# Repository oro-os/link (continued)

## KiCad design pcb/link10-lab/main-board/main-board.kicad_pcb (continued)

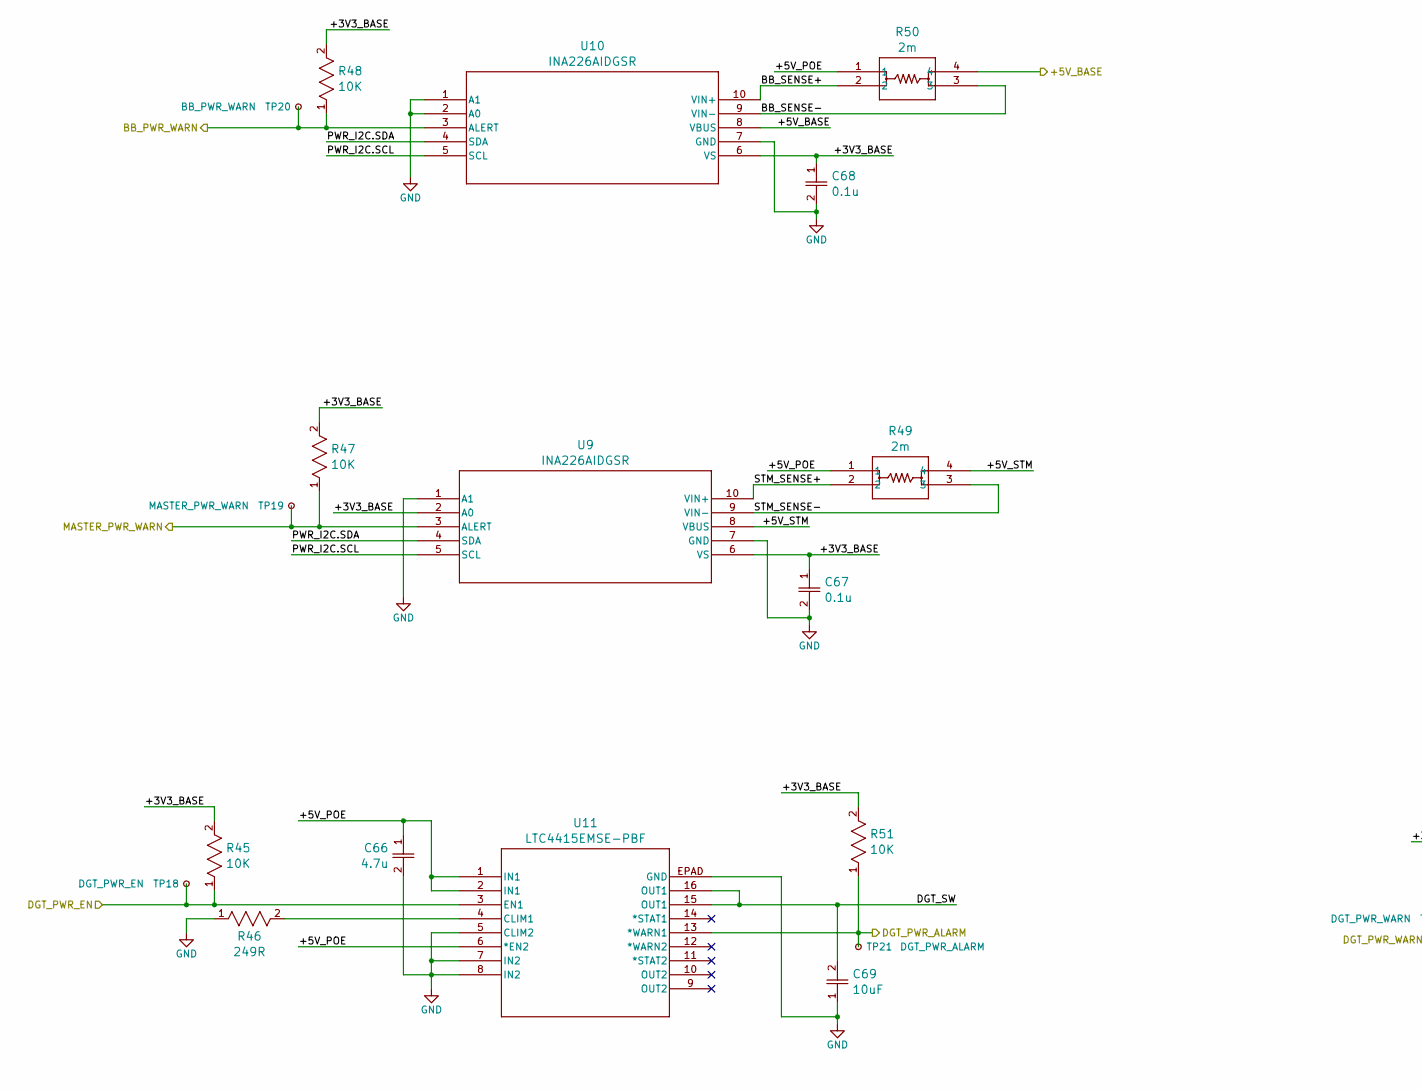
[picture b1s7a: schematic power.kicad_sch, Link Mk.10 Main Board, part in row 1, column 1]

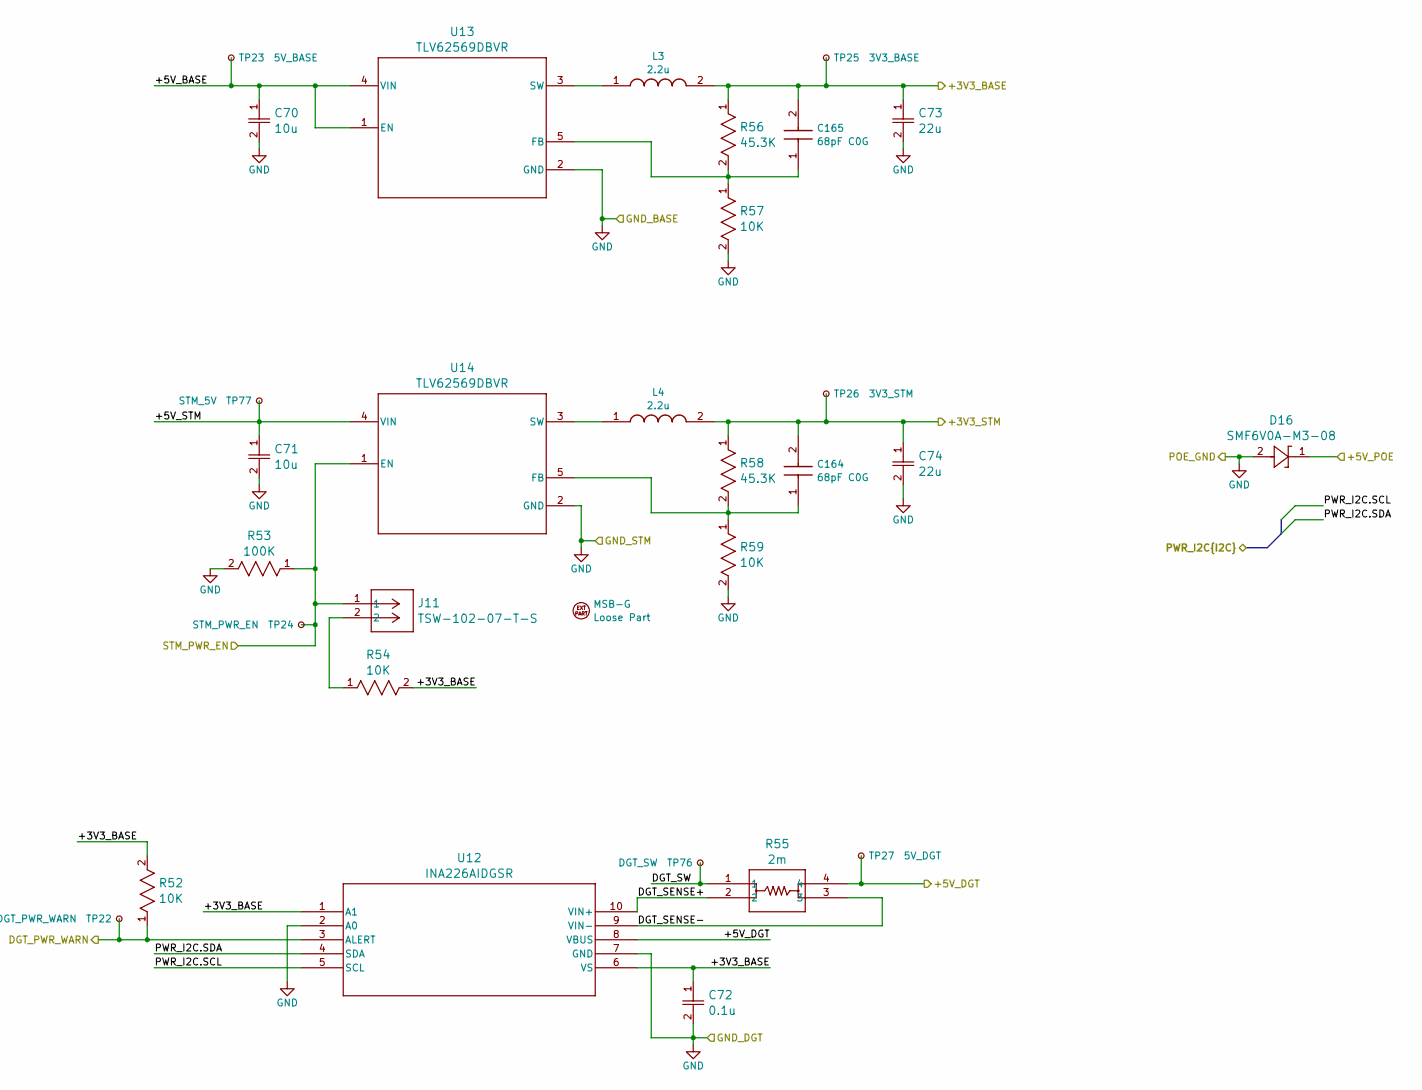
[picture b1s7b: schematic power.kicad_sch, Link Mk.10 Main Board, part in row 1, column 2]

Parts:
C66: 4.7u; OP_00014; Mouser P/N 187-CL05A475KP5NRNC; DigiKey ID 1276-1480-6-ND
C67, C68, C72: 0.1u; OP_0001Y; Mouser P/N 963-MSAST1L3YB5104KF; DigiKey ID 587-MSAST1L3YB5104KFNA01CT-ND
C69: 10uF; OP_0001M; Mouser P/N 81-GRM188R61E106MA3D; Mouser ID 81-GRM188R61E106MA3D
C70, C71: 10u; OP_0001M; Mouser P/N 81-GRM188R61E106MA3D; Mouser ID 81-GRM188R61E106MA3D
C73, C74: 22u; OP_00015; Mouser P/N 187-CL10A226MO7JZNC; DigiKey ID 1276-7076-1-ND
C164, C165: 68pF C0G; OP_0007M; Manufacturer_Part_Number GRT1555C1H680FA02J; Digi-Key P/N 490-GRT1555C1H680FA02JCT-ND, 490-GRT155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
D16: SMF6V0A-M3-08; OP_0003V; Mouser P/N 78-SMF6V0A-M3-08; Digi-Key P/N 112-SMF6V0A-M3-08CT-ND, 112-SMF6V0A-M3-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
EXT3: MSB-G; Mouser P/N 737-MSB-G; Digi-Key P/N 2057-MSB-G-ND
J11: TSW-102-07-T-S; OP_00079; Mouser P/N 200-TSW10207TS; Digi-Key P/N 612-TSW-102-07-T-S-ND
L3, L4: 2.2u; OP_0007C; Manufacturer_Part_Number MPXV1D0624L2R2; Digi-Key P/N 399-MPXV1D0624L2R2CT-ND, 399-MPXV1D0624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
R45, R47, R48, R51, R52, R54, R57, R59: 10K; OP_00021; Mouser P/N 708-RMCF0402FT10K0; DigiKey ID RMCF0402FT10K0CT-ND
R46: 249R; OP_0007B; Mouser P/N 71-CRCW0402-249-E3; Digi-Key P/N 541-249LCT-ND, 541-249LDKR-ND, 541-249L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
R49, R50, R55: 2m; OP_0002G; Mouser P/N 71-WSKW06122L000FEA; Mouser ID 71-WSKW06122L000FEA
R53: 100K; OP_00066; Mouser P/N 303-CQ03WAF1003T5E
R56, R58: 45.3K; OP_0007A; Mouser P/N 71-CRCW0402-45.3K-E3; Digi-Key P/N 541-45.3KLCT-ND, 541-45.3KLDKR-ND, 541-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
TP18: DGT_PWR_EN; TestPoint_Pad_D1.0mm
TP19: MASTER_PWR_WARN; TestPoint_Pad_D1.0mm
TP20: BB_PWR_WARN; TestPoint_Pad_D1.0mm
TP21: DGT_PWR_ALARM; TestPoint_Pad_D1.0mm
TP22: DGT_PWR_WARN; TestPoint_Pad_D1.0mm
TP23: 5V_BASE; TestPoint_Pad_2.0x2.0mm
TP24: STM_PWR_EN; TestPoint_Pad_D1.0mm
TP25: 3V3_BASE; TestPoint_Pad_2.0x2.0mm
TP26: 3V3_STM; TestPoint_Pad_2.0x2.0mm
TP27: 5V_DGT; TestPoint_Pad_2.0x2.0mm
TP76: DGT_SW; TestPoint_Pad_2.0x2.0mm
TP77: STM_5V; TestPoint_Pad_2.0x2.0mm
U9, U10, U12: INA226AIDGSR; OP_0001O; Mouser P/N 595-INA226AIDGSR; Mouser ID 595-INA226AIDGSR
U11: LTC4415EMSE-PBF; OP_0004S; Mouser P/N 584-LTC4415EMSE#PBF; Digi-Key P/N 505-LTC4415EMSE#PBF-ND
U13, U14: TLV62569DBVR; OP_00075; Mouser P/N 595-TLV62569DBVR; Digi-Key P/N 296-47360-1-ND, 296-47360-2-ND, 296-473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

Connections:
+3V3_BASE: C67.1, C68.1, C72.1, C73.1, C165.2, L3.2, R45.2, R47.2, R48.2, R51.2, R52.2, R54.2, R56.1, TP25.1 (1_1), U9.2 (A0), U9.6 (VS), U10.6 (VS), U12.1 (A1), U12.6 (VS); also elsewhere on the board
+3V3_STM: C74.1, C164.2, L4.2, R58.1, TP26.1 (1_1); also elsewhere on the board
+5V: C66.1, D16.1, R49.1, R50.1, U11.1 (IN1), U11.2 (IN1), U11.6 (*EN2); also elsewhere on the board
+5V_BASE: C70.1, R50.4, TP23.1 (1_1), U10.8 (VBUS), U13.1 (EN), U13.4 (VIN); also elsewhere on the board
+5V_DGT: R55.4, TP27.1 (1_1), U12.8 (VBUS); also elsewhere on the board
/BB_I2C1.SCL: U9.5 (SCL), U10.5 (SCL), U12.5 (SCL); also elsewhere on the board
/BB_I2C1.SDA: U9.4 (SDA), U10.4 (SDA), U12.4 (SDA); also elsewhere on the board
/Baseboard/BB_PWR_WARN: R48.1, TP20.1 (1_1), U10.3 (ALERT); also elsewhere on the board
/Baseboard/DGT_PWR_ALARM: R51.1, TP21.1 (1_1), U11.13 (*WARN1); also elsewhere on the board
/Baseboard/DGT_PWR_EN: R45.1, TP18.1 (1_1), U11.3 (EN1); also elsewhere on the board
/Baseboard/DGT_PWR_WARN: R52.1, TP22.1 (1_1), U12.3 (ALERT); also elsewhere on the board
/Baseboard/MASTER_PWR_EN: J11.1, R53.1, TP24.1 (1_1), U14.1 (EN); also elsewhere on the board
/Baseboard/MASTER_PWR_WARN: R47.1, TP19.1 (1_1), U9.3 (ALERT); also elsewhere on the board
/Power/+5V_STM: C71.1, R49.4, TP77.1 (1_1), U9.8 (VBUS), U14.4 (VIN)
/Power/BB_SENSE+: R50.2, U10.10 (VIN+)
/Power/BB_SENSE-: R50.3, U10.9 (VIN-)
/Power/DGT_SENSE+: R55.2, U12.10 (VIN+)
/Power/DGT_SENSE-: R55.3, U12.9 (VIN-)
/Power/DGT_SW: C69.2, R55.1, TP76.1 (1_1), U11.15 (OUT1), U11.16 (OUT1)
/Power/STM_SENSE+: R49.2, U9.10 (VIN+)
/Power/STM_SENSE-: R49.3, U9.9 (VIN-)
GND: C66.2, C67.2, C68.2, C69.1, C70.2, C71.2, C72.2, C73.2, C74.2, D16.2, R46.1, R53.2, R57.2, R59.2, U9.1 (A1), U9.7 (GND), U10.1 (A1), U10.2 (A0), U10.7 (GND), U11.5 (CLIM2), U11.7 (IN2), U11.8 (IN2), U11.EPAD (GND), U12.2 (A0), U12.7 (GND), U13.2 (GND), U14.2 (GND); also elsewhere on the board
unnamed: J11.2, R54.1
unnamed: R46.2, U11.4 (CLIM1)
unnamed: C165.1, R56.2, R57.1, U13.5 (FB)
unnamed: L3.1, U13.3 (SW)
unnamed: C164.1, R58.2, R59.1, U14.5 (FB)
unnamed: L4.1, U14.3 (SW)

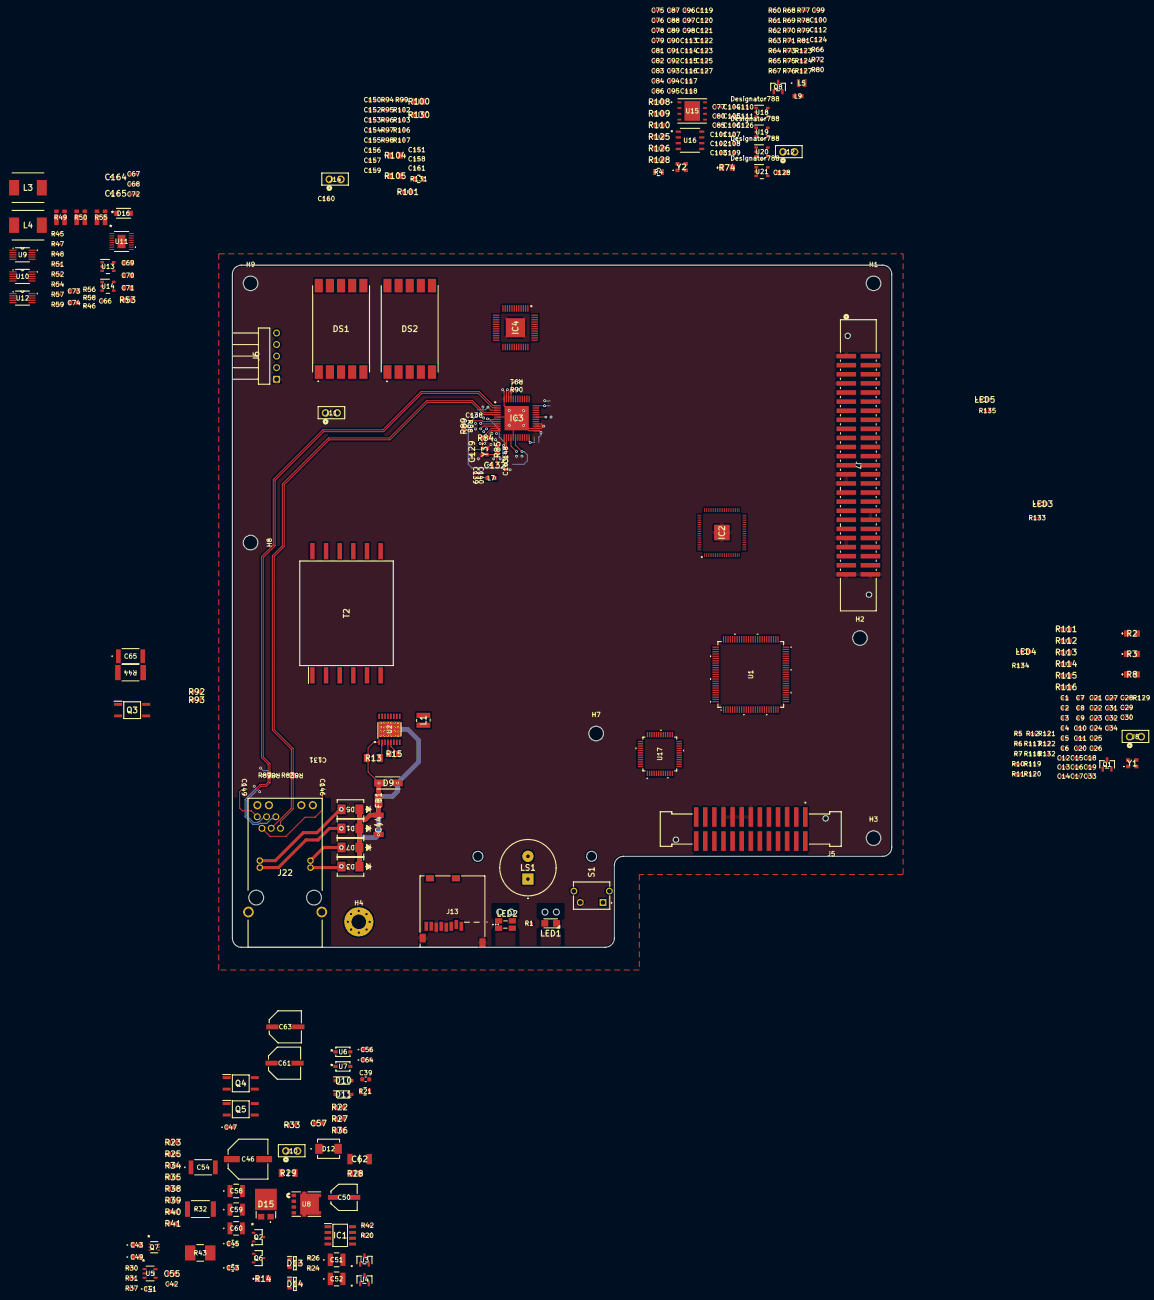
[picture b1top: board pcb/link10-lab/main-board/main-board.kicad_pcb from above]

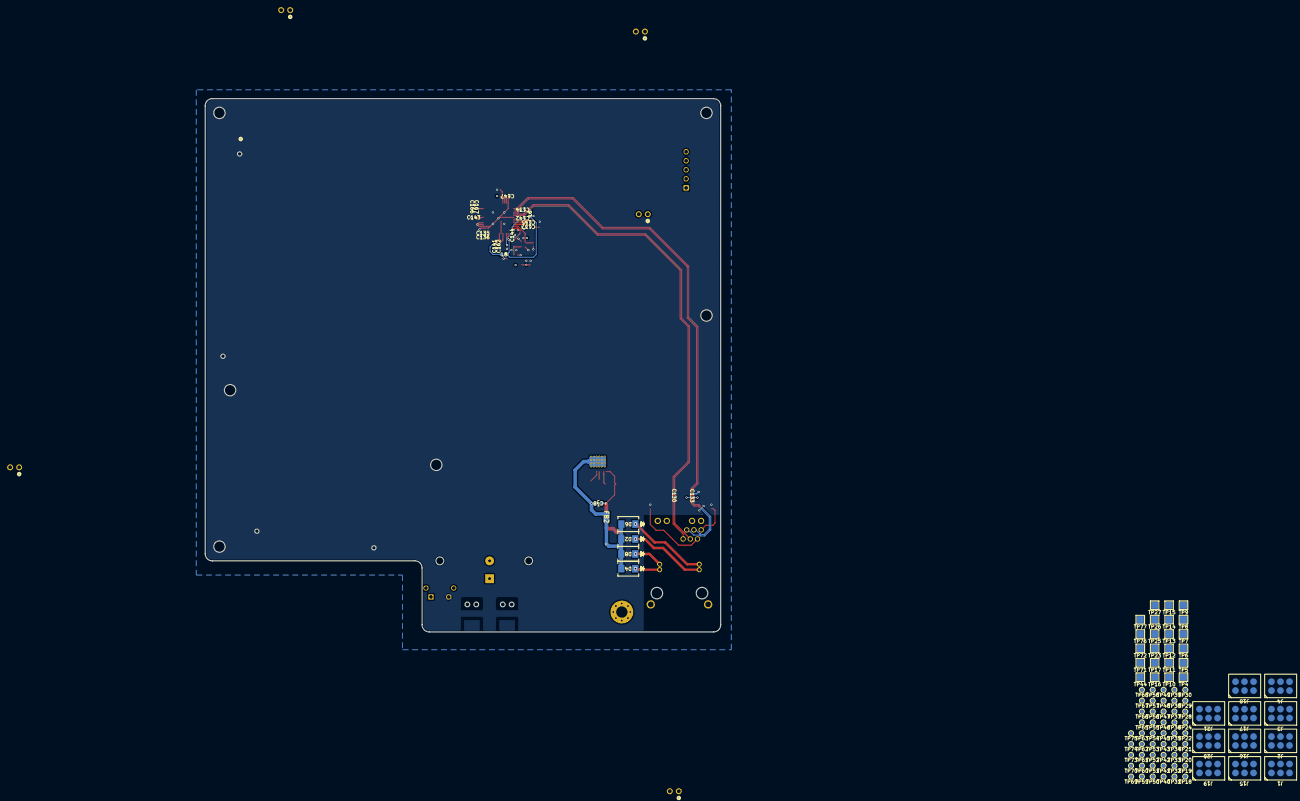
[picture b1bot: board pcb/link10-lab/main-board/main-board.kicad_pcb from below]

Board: 8 copper layers, 145.0 x 150.0 mm, 467 parts (107 on the bottom side), 257 nets.

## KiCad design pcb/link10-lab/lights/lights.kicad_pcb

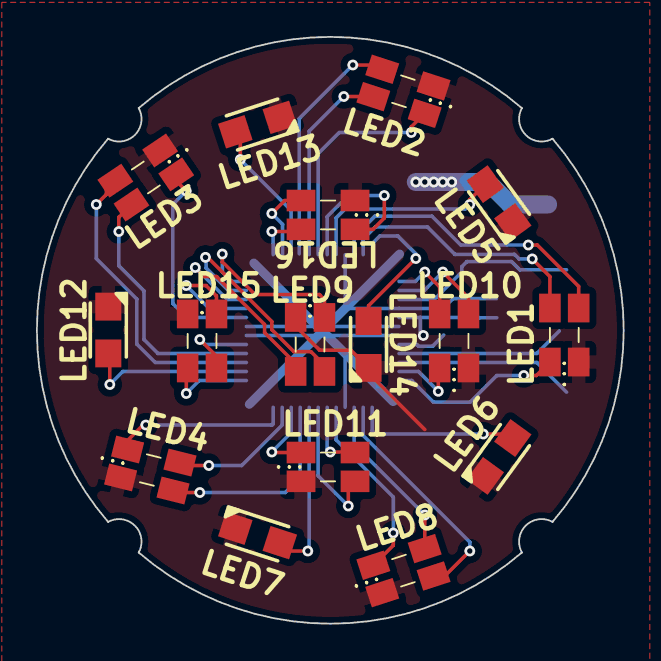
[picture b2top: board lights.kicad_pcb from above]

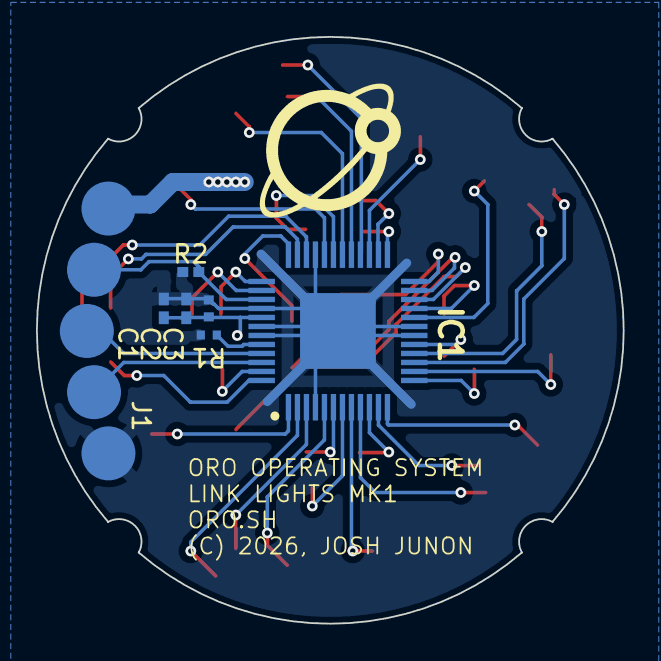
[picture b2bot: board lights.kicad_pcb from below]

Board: 2 copper layers, 32.6 x 32.6 mm, 23 parts (7 on the bottom side), 42 nets.

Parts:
C1: 1u; OP_0001R
C2: 0.1u; OP_0001Y
C3: 0.01u; OP_0000F
IC1: IS31FL3236A-TQLS4-TR; OP_0001Q
J1: Conn_01x05; Wire Jack 5p 18g
LED1, LED2, LED3, LED4, LED8, LED9, LED10, LED11, LED15, LED16: 150120M173000; OP_00006
LED5, LED6, LED7, LED12, LED13, LED14: CLM3C-WKW-CXAYA453; OP_00016
R1: 4.7K; OP_0001C
R2: 10K; OP_00021

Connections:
/+3V3: C1.1, C2.1, C3.1, IC1.41 (VCC), J1.1, LED1.2 (A_G), LED2.2 (A_G), LED3.2 (A_G), LED4.2 (A_G), LED5.1 (A), LED6.1 (A), LED7.1 (A), LED8.2 (A_G), LED9.2 (A_G), LED10.2 (A_G), LED11.2 (A_G), LED12.1 (A), LED13.1 (A), LED14.1 (A), LED15.2 (A_G), LED16.2 (A_G)
/EN: IC1.39 (SDB), J1.2, R2.2
/GND: C1.2, C2.2, C3.2, IC1.4 (GND_1), IC1.18 (GND_2), IC1.19 (GND_3), IC1.33 (GND_4), IC1.40 (AD), IC1.42 (GND_5), IC1.43 (GND_6), IC1.49 (EP), J1.5, R1.2, R2.1
/O1: IC1.47 (OUT1), LED10.1 (K_B)
/O2: IC1.48 (OUT2), LED1.1 (K_B)
/O3: IC1.1 (OUT3), LED6.2 (K)
/O4: IC1.2 (OUT4), LED8.3 (K_G)
/O5: IC1.3 (OUT5), LED8.4 (K_R)
/O6: IC1.5 (OUT6), LED8.1 (K_B)
/O7: IC1.6 (OUT7), LED11.4 (K_R)
/O8: IC1.7 (OUT8), LED11.3 (K_G)
/O9: IC1.8 (OUT9), LED7.2 (K)
/O10: IC1.9 (OUT10), LED4.3 (K_G)
/O11: IC1.10 (OUT11), LED11.1 (K_B)
/O12: IC1.11 (OUT12), LED4.4 (K_R)
/O13: IC1.12 (OUT13), LED4.1 (K_B)
/O14: IC1.13 (OUT14), LED15.3 (K_G)
/O15: IC1.14 (OUT15), LED12.2 (K)
/O16: IC1.15 (OUT16), LED3.3 (K_G)
/O17: IC1.16 (OUT17), LED3.4 (K_R)
/O18: IC1.17 (OUT18), LED15.4 (K_R)
/O19: IC1.20 (OUT19), LED3.1 (K_B)
/O20: IC1.21 (OUT20), LED15.1 (K_B)
/O21: IC1.22 (OUT21), LED9.3 (K_G)
/O22: IC1.23 (OUT22), LED9.4 (K_R)
/O23: IC1.24 (OUT23), LED9.1 (K_B)
/O24: IC1.25 (OUT24), LED16.4 (K_R)
/O25: IC1.26 (OUT25), LED16.3 (K_G)
/O26: IC1.27 (OUT26), LED13.2 (K)
/O27: IC1.28 (OUT27), LED2.3 (K_G)
/O28: IC1.29 (OUT28), LED2.4 (K_R)
/O29: IC1.30 (OUT29), LED2.1 (K_B)
/O30: IC1.31 (OUT30), LED16.1 (K_B)
/O31: IC1.32 (OUT31), LED5.2 (K)
/O32: IC1.34 (OUT32), LED1.3 (K_G)
/O33: IC1.35 (OUT33), LED1.4 (K_R)
/O34: IC1.36 (OUT34), LED14.2 (K)
/O35: IC1.37 (OUT35), LED10.4 (K_R)
/O36: IC1.38 (OUT36), LED10.3 (K_G)
/SCL: IC1.46 (SCL), J1.4
/SDA: IC1.45 (SDA), J1.3
unnamed: IC1.44 (R_EXT), R1.1

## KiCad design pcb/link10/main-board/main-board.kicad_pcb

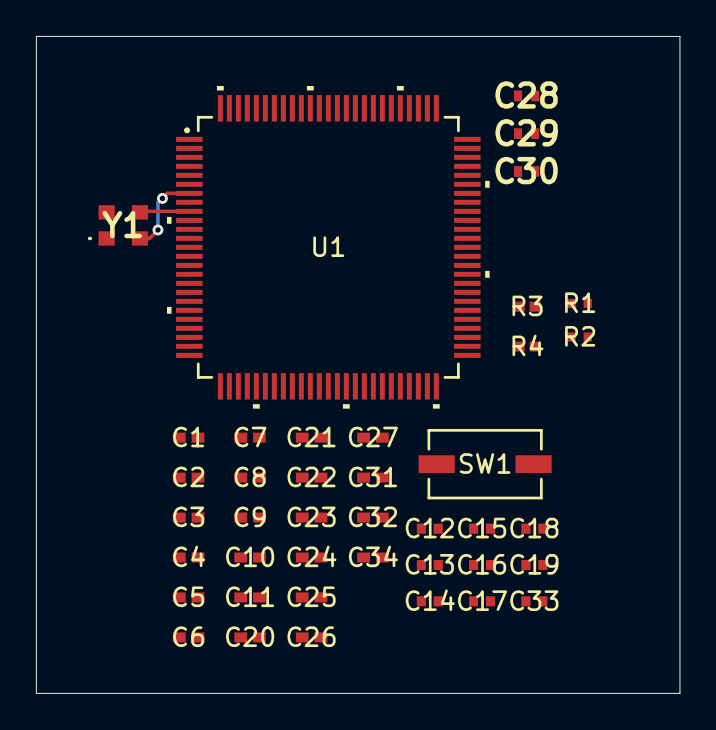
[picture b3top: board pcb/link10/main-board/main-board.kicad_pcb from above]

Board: 2 copper layers, 35.8 x 36.5 mm, 41 parts (0 on the bottom side), 10 nets.

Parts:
C1, C2, C3: 2.2u; CAP_MK105_V_TAY
C4, C5, C6, C7, C8, C9, C10, C11, C32, C34: 0.1u; CAP_MSAS1L-3_TAY
C12, C13, C14, C15, C16, C17, C18, C19, C33: 0.01u; CAP_0402_N_WAL
C20, C21, C22, C23, C24, C25, C26, C27, C31: 1u; cap_UMK105 CG080CV-F_TAY
C28, C29, C30: 4.7u; GRM15x
R1, R2: 4.7K; RES_CRCW_0402_VIS-L
R3, R4: 10K; STA_RMCF0402_STP
SW1: TL6400AF160QJ; SW_TL6400AF260QJ_EWI
U1: STM32F479VGT6; LQFP100_STM
Y1: ECS-2520SMV-240-FP-TR; ECS2520SMV240FPTR

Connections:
/Microcontroller/+3V3: C4.1, C5.1, C6.1, C7.1, C8.1, C9.1, C10.1, C11.1, C12.1, C13.1, C14.1, C15.1, C16.1, C17.1, C18.1, C19.1, C20.1, C21.1, C22.1, C23.1, C24.1, C25.1, C26.1, C27.1, C28.1, C29.1, C30.1, C31.2, C32.2, C33.2, R1.1, R2.1, R3.2, R4.2, U1.3 (VBAT), U1.8 (VDD), U1.17 (VREF+), U1.18 (VDDA), U1.24 (VDD), U1.45 (VDD), U1.55 (VDDDSI), U1.65 (VDDUSB), U1.77 (VDD), U1.100 (VDD), Y1.4 (VDD)
/Microcontroller/GND: C1.1, C2.1, C3.1, C4.2, C5.2, C6.2, C7.2, C8.2, C9.2, C10.2, C11.2, C12.2, C13.2, C14.2, C15.2, C16.2, C17.2, C18.2, C19.2, C20.2, C21.2, C22.2, C23.2, C24.2, C25.2, C26.2, C27.2, C28.2, C29.2, C30.2, C31.1, C32.1, C33.1, C34.2, SW1.2, U1.2 (VSS), U1.7 (VSS), U1.16 (VSSA), U1.23 (VSS), U1.44 (VSS), U1.59 (VSSDSI), U1.78 (VSS), Y1.2 (GND)
/Microcontroller/I2C1.SCL: R2.2, U1.98 (PB8)
/Microcontroller/I2C1.SDA: R1.2, U1.99 (PB9)
unnamed: C34.1, R4.1, SW1.1, U1.11 (NRST)
unnamed: U1.9 (PH0), Y1.3 (OUTPUT)
unnamed: C1.2, U1.43 (VCAP1)
unnamed: C2.2, U1.76 (VCAP2)
unnamed: C3.2, U1.56 (VCAPDSI), U1.62 (VDD12DSI)
unnamed: R3.1, Y1.1 (TRI-STATE)

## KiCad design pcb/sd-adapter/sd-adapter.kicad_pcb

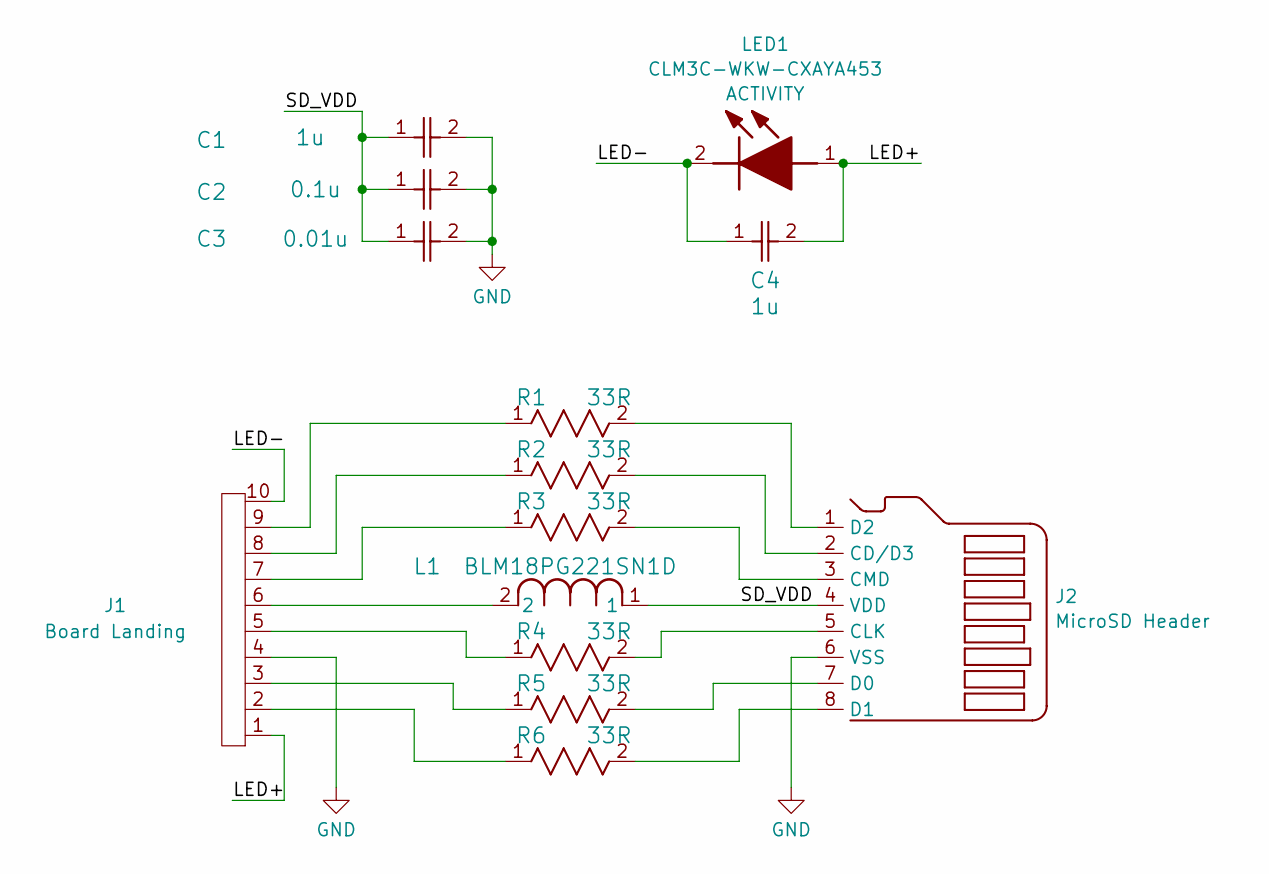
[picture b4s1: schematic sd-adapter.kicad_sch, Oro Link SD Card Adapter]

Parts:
C1, C4: 1u; cap_UMK105 CG080CV-F_TAY; DigiKey ID 587-3766-1-ND
C2: 0.1u; CAP_MSAS1L-3_TAY; DigiKey ID 587-MSAST1L3YB5104KFNA01CT-ND
C3: 0.01u; CAP_0402_N_WAL; Mouser ID 791-0402B103J160CT
J1: Board Landing; OroSDCardCouplingPadBoardSide
J2: MicroSD Header; SDCardOutlinePadsTop
L1: BLM18PG221SN1D; IND_BLM18_0603_MUR; DigiKey ID 490-5221-1-ND
LED1: CLM3C-WKW-CXAYA453; CLM3CWKWCXAYA453; Manufacturer_Part_Number CLM3C-WKW-CXAYA453; Mouser Part Number 941-CLM3CWKWCXAYA453
R1, R2, R3, R4, R5, R6: 33R; RES_0510_SUS; DigiKey ID RR05R33DCT-ND

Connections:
/LED+: C4.2, J1.1, LED1.1 (A); also elsewhere on the board
/LED-: C4.1, J1.10, LED1.2 (K); also elsewhere on the board
/SD_VDD: C1.1, C2.1, C3.1, J2.4 (VDD), L1.1
GND: C1.2, C2.2, C3.2, J1.4, J2.6 (VSS)
unnamed: J1.2, R6.1
unnamed: J1.3, R5.1
unnamed: J1.5, R4.1
unnamed: J1.6, L1.2
unnamed: J1.7, R3.1
unnamed: J1.8, R2.1
unnamed: J1.9, R1.1
unnamed: J2.2 (CD/D3), R2.2
unnamed: J2.5 (CLK), R4.2
unnamed: J2.3 (CMD), R3.2
unnamed: J2.7 (D0), R5.2
unnamed: J2.8 (D1), R6.2
unnamed: J2.1 (D2), R1.2

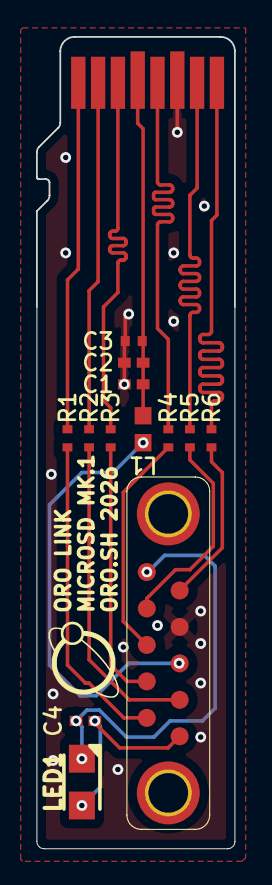
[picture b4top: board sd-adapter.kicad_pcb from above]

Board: 2 copper layers, 11.0 x 45.1 mm, 15 parts (1 on the bottom side), 17 nets.

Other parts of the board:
LED2: CLM3C-WKW-CXAYA453; CLM3CWKWCXAYA453

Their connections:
/LED+: LED2.1 (A); also elsewhere on the board
/LED-: LED2.2 (K); also elsewhere on the board

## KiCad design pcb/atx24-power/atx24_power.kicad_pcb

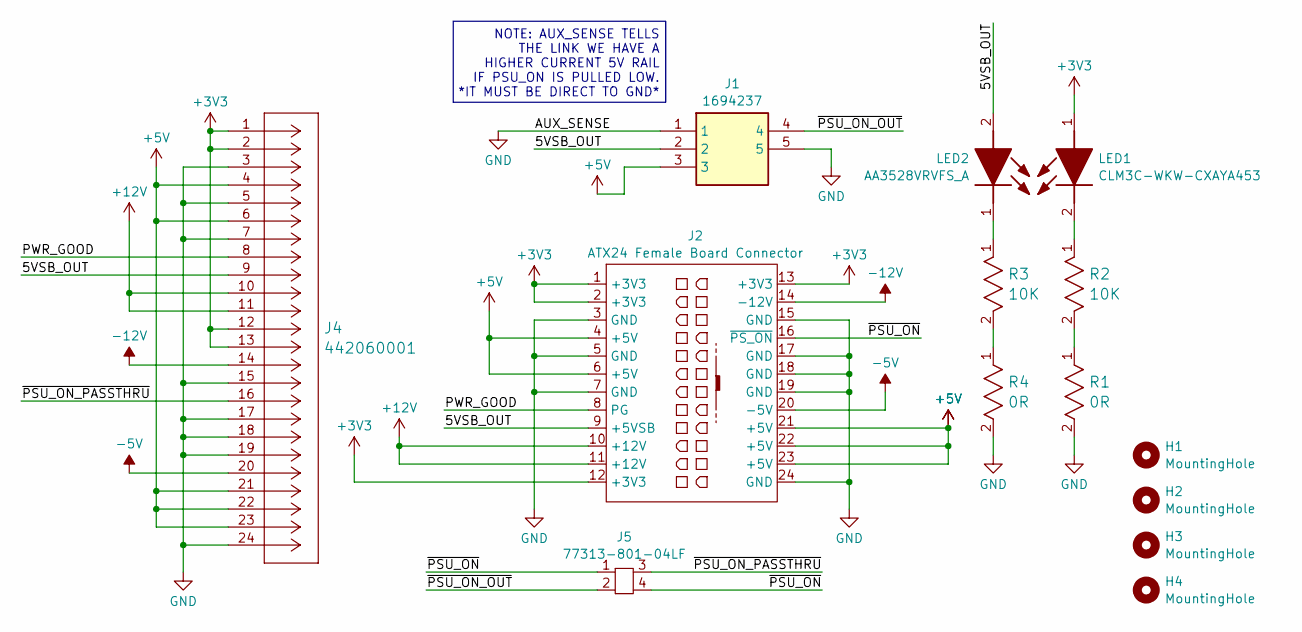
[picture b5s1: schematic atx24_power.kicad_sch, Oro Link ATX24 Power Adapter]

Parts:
H1, H2, H3, H4: MountingHole; MountingHole_3.2mm_M3
J1: 1694237; Manufacturer_Part_Number 1694237; Mouser Part Number 651-1694237
J2: ATX24 Female Board Connector; ATX24_Female_Board_Connector
J4: 442060001; CONN_SDA-44206-001_24_BP_MOL; Mouser ID 538-44206-0001
J5: 77313-801-04LF; 2x2 4p 2.54 pitch straight; Mouser ID Number 649-77313-801-04LF
LED1: CLM3C-WKW-CXAYA453; CLM3CWKWCXAYA453; Manufacturer_Part_Number CLM3C-WKW-CXAYA453; Mouser Part Number 941-CLM3CWKWCXAYA453
LED2: AA3528VRVFS_A; AA3528VRVFSA; Manufacturer_Part_Number AA3528VRVFS/A; Mouser Part Number 604-AA3528VRVFS/A
R1, R4: 0R; RES_RK73Z1E_KOA; DigiKey ID 2019-RK73Z1ETTPCT-ND
R2, R3: 10K; STA_RMCF0402_STP; DigiKey ID RMCF0402FT10K0CT-ND

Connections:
+3V3: J2.1 (+3V3), J2.2 (+3V3), J2.12 (+3V3), J2.13 (+3V3), J4.1, J4.2, J4.12, J4.13, LED1.1 (A)
+5V: J1.3, J2.4 (+5V), J2.6 (+5V), J2.21 (+5V), J2.22 (+5V), J2.23 (+5V), J4.4, J4.6, J4.21, J4.22, J4.23
+12V: J2.10 (+12V), J2.11 (+12V), J4.10, J4.11
-5V: J2.20 (-5V), J4.20
-12V: J2.14 (-12V), J4.14
/5VSB_OUT: J1.2, J2.9 (+5VSB), J4.9, LED2.2 (A)
/PWR_GOOD: J2.8 (PG), J4.8
/~PSU_ON_OUT: J1.4, J5.2
/~PSU_ON_PASSTHRU: J4.16, J5.3
/~PSU_ON: J2.16 (~PS_ON), J5.1, J5.4
GND: J1.1, J1.5, J2.3 (GND), J2.5 (GND), J2.7 (GND), J2.15 (GND), J2.17 (GND), J2.18 (GND), J2.19 (GND), J2.24 (GND), J4.3, J4.5, J4.7, J4.15, J4.17, J4.18, J4.19, J4.24, R1.2, R4.2
unnamed: LED1.2 (K), R2.1
unnamed: LED2.1 (K), R3.1
unnamed: R1.1, R2.2
unnamed: R3.2, R4.1

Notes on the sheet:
NOTE: AUX_SENSE TELLS THE LINK WE HAVE A HIGHER CURRENT 5V RAIL IF PSU_ON IS PULLED LOW. *IT MUST BE DIRECT TO GND*

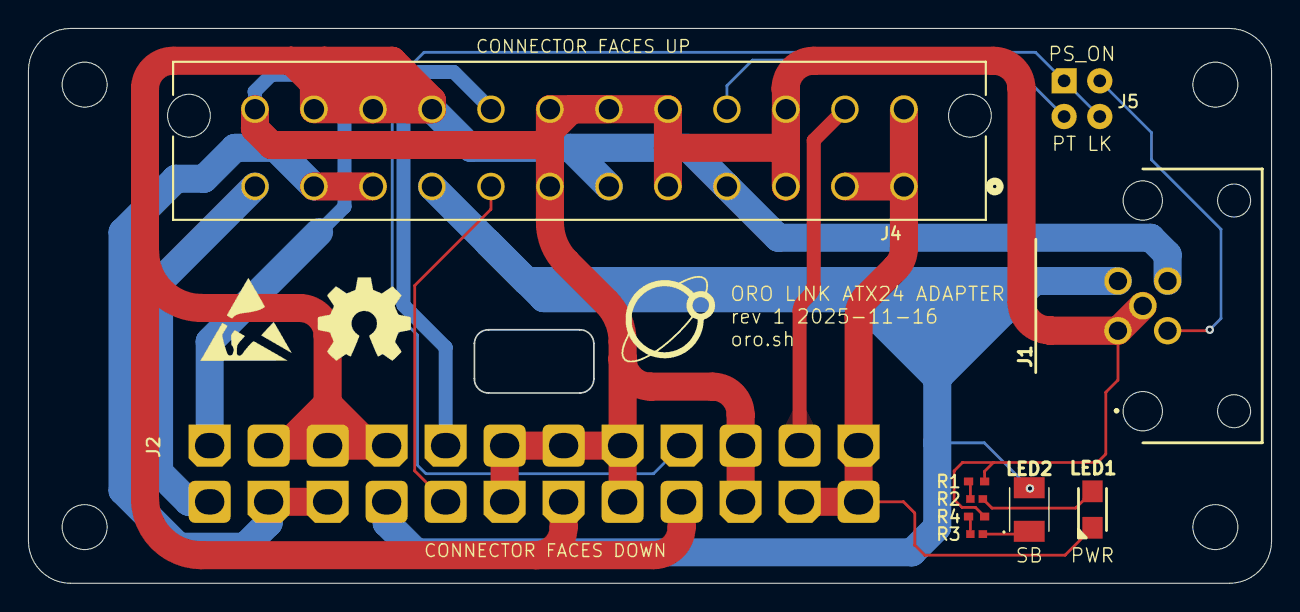
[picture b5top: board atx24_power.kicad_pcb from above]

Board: 2 copper layers, 88.5 x 39.5 mm, 14 parts (1 on the bottom side), 15 nets.
